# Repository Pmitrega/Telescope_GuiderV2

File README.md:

## Development Environment setup

Setup docker:
<pre>
sudo apt install -y docker.io
sudo usermod -aG docker $USER
exec su -l $USER
docker pull --platform linux/arm64 debian:11
</pre>

Enable multiarchitecture emulation and verify it:
<pre>
docker run --rm --privileged multiarch/qemu-user-static --reset -p yes
docker run --rm --privileged multiarch/qemu-user-static --version
</pre>

Now run crosscompile script, first it setup container with :
<pre>
./cross_compile.sh
</pre>

## Target Environment setup
Setup MQTT broker
<pre>
sudo apt update
sudo apt install -y mosquitto mosquitto-clients
</pre>
Enable mosquitto as service
<pre>
sudo systemctl enable mosquitto
sudo systemctl start mosquitto
sudo systemctl status mosquitto
</pre>
To test broker on one console run:
<pre>
mosquitto_sub -t test/topic
</pre>
On other use, after this message on previous one shoud show.
<pre>
mosquitto_pub -t test/topic -m "Hello MQTT"
</pre>

### Mosquito configuration
Now enable websockets and free access:
<pre>
sudo nano /etc/mosquitto/mosquitto.conf
</pre>
Add following lines:
<pre>
listener 1883
allow_anonymous true
listener 9001
</pre>

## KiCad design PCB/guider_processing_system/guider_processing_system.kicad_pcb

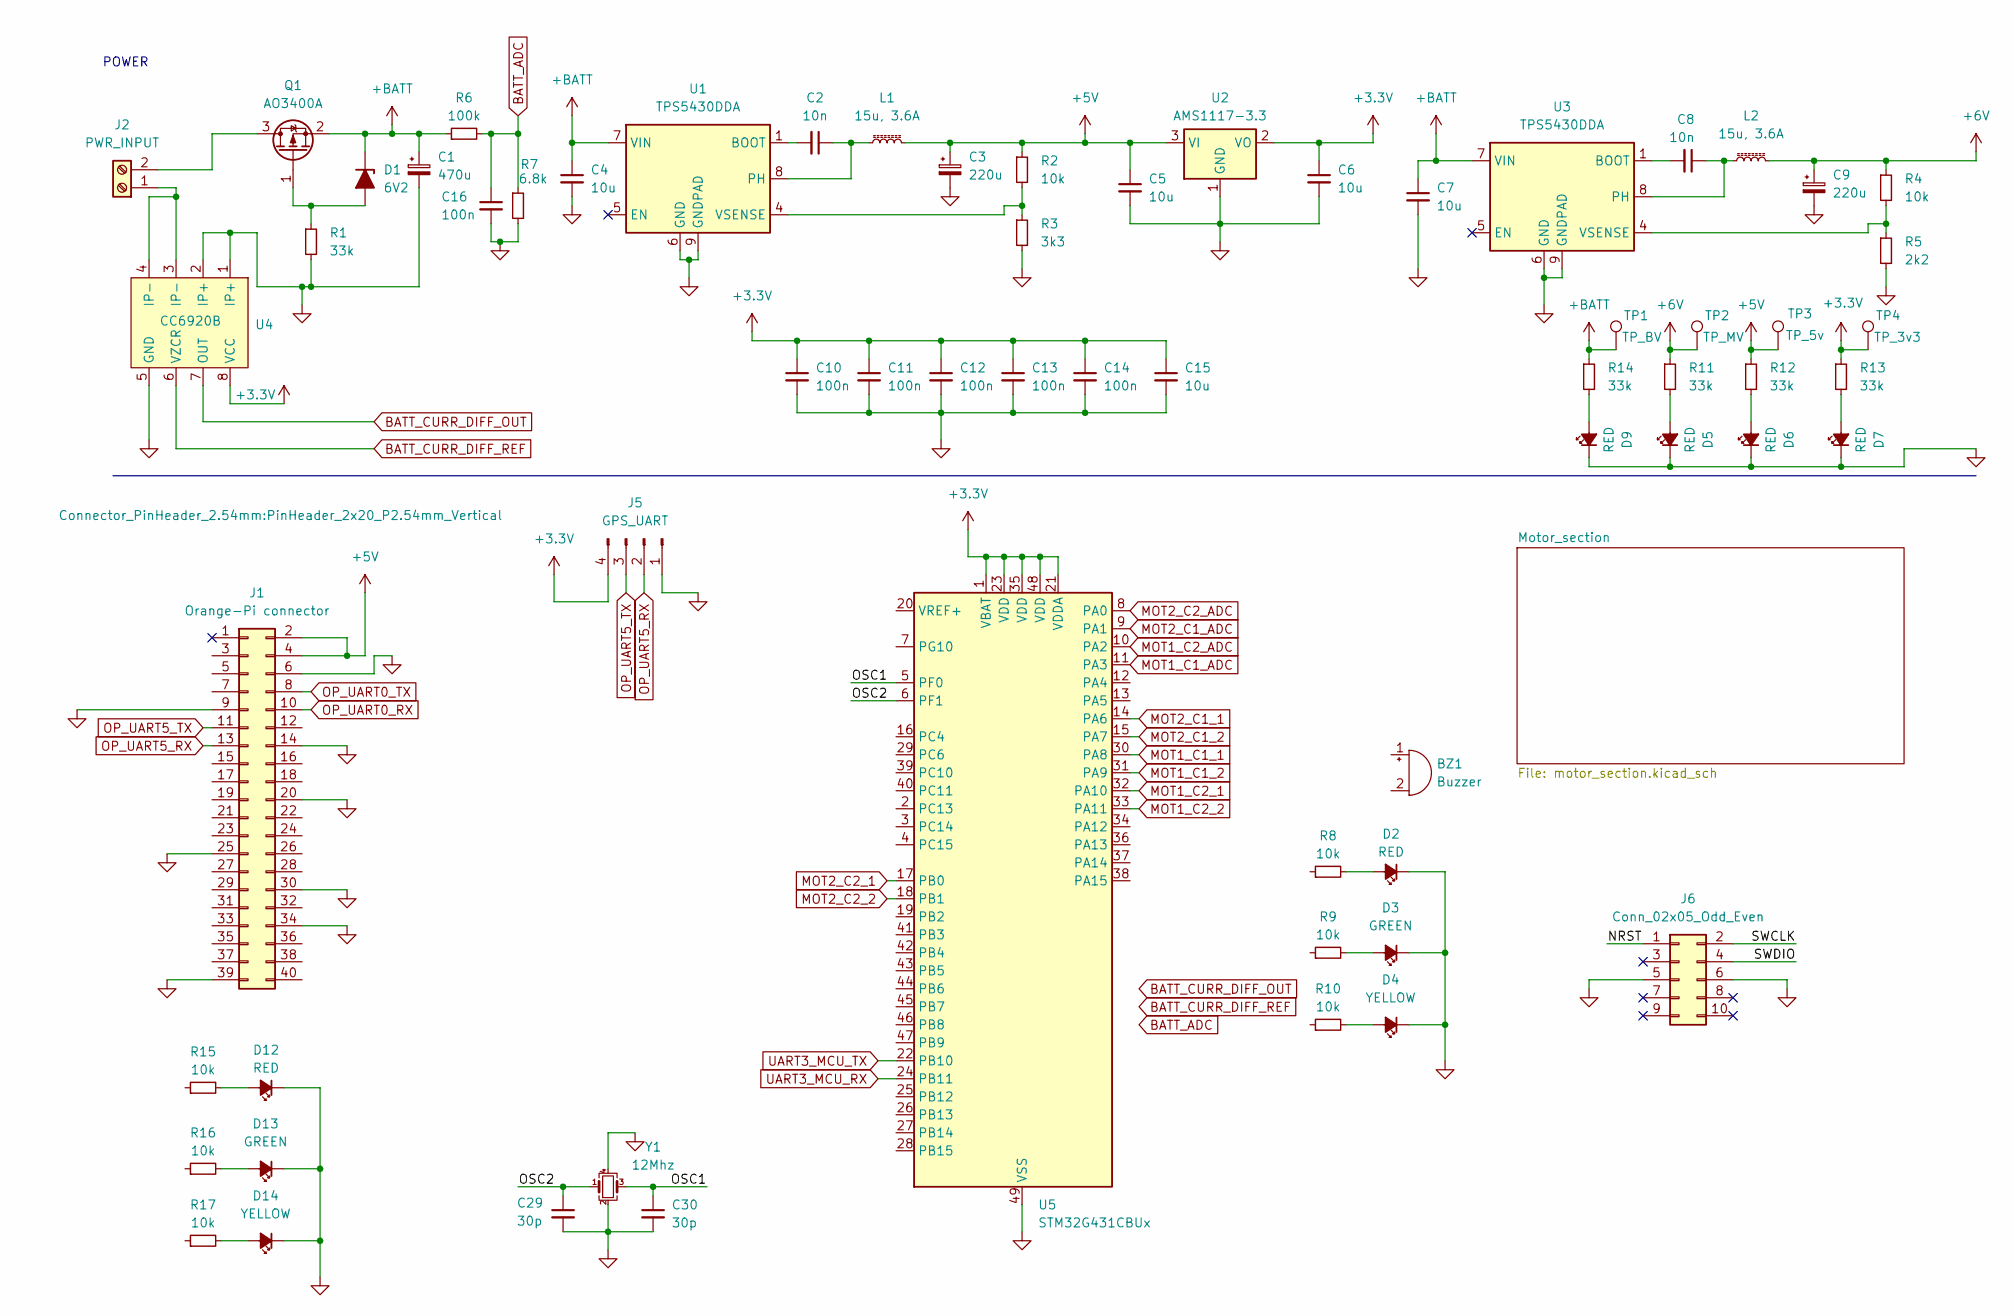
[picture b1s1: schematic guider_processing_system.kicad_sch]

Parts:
BZ1: Buzzer; Buzzer_15x7.5RM7.6
C1: 470u; CP_Radial_D10.0mm_P5.00mm
C2: 10n; C_0603_1608Metric; LCSC C57112
C3, C9: 220u; CP_Radial_D6.3mm_P2.50mm
C4, C7: 10u; C_1206_3216Metric; LCSC C13585
C5, C6, C15: 10u; C_0603_1608Metric; LCSC C1691
C8: 10n; C_0603_1608Metric
C10, C11, C12, C13, C14, C16: 100n; C_0603_1608Metric; LCSC C14663
C29, C30: 30p; C_0603_1608Metric; LCSC C1658
D1: 6V2; D_SOD-323; LCSC C19077457
D2, D5, D6, D7, D9, D12: RED; LED_0805_2012Metric; LCSC C84256
D3, D13: GREEN; LED_0805_2012Metric; LCSC C2297
D4, D14: YELLOW; LED_0805_2012Metric; LCSC C2296
J1: Orange-Pi connector; PinHeader_2x20_P2.54mm_Vertical
J2: PWR_INPUT; TerminalBlock_bornier-2_P5.08mm
J5: GPS_UART; JST_XH_B4B-XH-AM_1x04_P2.50mm_Vertical
J6: Conn_02x05_Odd_Even; IDC-Header_2x05_P2.54mm_Vertical
L1, L2: 15u, 3.6A; L_Sunlord_MWSA1004S; LCSC C436488
Q1: AO3400A; TSOT-23; LCSC C20917
R1, R11, R12, R13, R14: 33k; R_0603_1608Metric; LCSC C4216
R2, R4, R8, R9, R10, R15, R16, R17: 10k; R_0603_1608Metric; LCSC C4216
R3: 3k3; R_0603_1608Metric; LCSC C4216
R5: 2k2; R_0603_1608Metric; LCSC C4216
R6: 100k; R_0603_1608Metric; LCSC C4216
R7: 6.8k; R_0603_1608Metric; LCSC C4216
TP1: TP_BV
TP2: TP_MV
TP3: TP_5v
TP4: TP_3v3
U1, U3: TPS5430DDA; TI_SO-PowerPAD-8_ThermalVias; LCSC C9864
U2: AMS1117-3.3; SOT-223-3_TabPin2; LCSC C6186
U4: CC6920B; SOP-8_3.9x4.9mm_P1.27mm
U5: STM32G431CBUx; QFN-48-1EP_7x7mm_P0.5mm_EP5.6x5.6mm
Y1: 12Mhz; Crystal_SMD_3225-4Pin_3.2x2.5mm; LCSC C9002

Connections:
+3.3V: C6.1, C10.1, C11.1, C12.1, C13.1, C14.1, C15.1, J5.4, R13.1, TP4.1, U2.2 (VO), U4.8 (VCC), U5.1 (VBAT), U5.21 (VDDA), U5.23 (VDD), U5.35 (VDD), U5.48 (VDD)
+5V: C3.1, C5.1, J1.2, J1.4, L1.2, R2.1, R12.1, TP3.1, U2.3 (VI)
+6V: C9.1, L2.2, R4.1, R11.1, TP2.1; also elsewhere on the board
+BATT: C1.1, C4.1, C7.1, D1.1 (K), Q1.2 (S), R6.1, R14.1, TP1.1, U1.7 (VIN), U3.7 (VIN)
/NRST: J6.1
/OSC1: C30.1, U5.5 (PF0), Y1.3
/OSC2: C29.1, U5.6 (PF1), Y1.1
/SWCLK: J6.2
/SWDIO: J6.4
BATT_ADC: C16.1, R6.2, R7.1
BATT_CURR_DIFF_OUT: U4.7 (OUT)
BATT_CURR_DIFF_REF: U4.6 (VZCR)
GND: C1.2, C3.2, C4.2, C5.2, C6.2, C7.2, C9.2, C10.2, C11.2, C12.2, C13.2, C14.2, C15.2, C16.2, C29.2, C30.2, D2.1 (K), D3.1 (K), D4.1 (K), D5.1 (K), D6.1 (K), D7.1 (K), D9.1 (K), D12.1 (K), D13.1 (K), D14.1 (K), J1.6, J1.9, J1.14, J1.20, J1.25, J1.30, J1.34, J1.39, J5.1, J6.5, J6.6, R1.2, R3.2, R5.2, R7.2, U1.6 (GND), U1.9 (GNDPAD), U2.1 (GND), U3.6 (GND), U3.9 (GNDPAD), U4.1 (IP+), U4.2 (IP+), U4.5 (GND), U5.49 (VSS), Y1.2, Y1.4; also elsewhere on the board
MOT1_C1_1: U5.30 (PA8); also elsewhere on the board
MOT1_C1_2: U5.31 (PA9); also elsewhere on the board
MOT1_C2_1: U5.32 (PA10); also elsewhere on the board
MOT1_C2_2: U5.33 (PA11); also elsewhere on the board
MOT2_C1_1: U5.14 (PA6); also elsewhere on the board
MOT2_C1_2: U5.15 (PA7); also elsewhere on the board
MOT2_C2_1: U5.17 (PB0); also elsewhere on the board
MOT2_C2_2: U5.18 (PB1); also elsewhere on the board
unnamed: D1.2 (A), Q1.1 (G), R1.1
unnamed: D2.2 (A), R8.2
unnamed: D3.2 (A), R9.2
unnamed: D4.2 (A), R10.2
unnamed: D5.2 (A), R11.2
unnamed: D6.2 (A), R12.2
unnamed: D7.2 (A), R13.2
unnamed: D9.2 (A), R14.2
unnamed: D12.2 (A), R15.2
unnamed: D13.2 (A), R16.2
unnamed: D14.2 (A), R17.2
unnamed: J2.1, U4.3 (IP-), U4.4 (IP-)
unnamed: J2.2, Q1.3 (D)
unnamed: C2.2, U1.1 (BOOT)
unnamed: C2.1, L1.1, U1.8 (PH)
unnamed: R2.2, R3.1, U1.4 (VSENSE)
unnamed: C8.2, U3.1 (BOOT)
unnamed: C8.1, L2.1, U3.8 (PH)
unnamed: R4.2, R5.1, U3.4 (VSENSE)
OP_UART0_RX: J1.10
OP_UART0_TX: J1.8
OP_UART5_RX: J1.13, J5.2
OP_UART5_TX: J1.11, J5.3
UART3_MCU_RX: U5.24 (PB11)
UART3_MCU_TX: U5.22 (PB10)

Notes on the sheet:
POWER

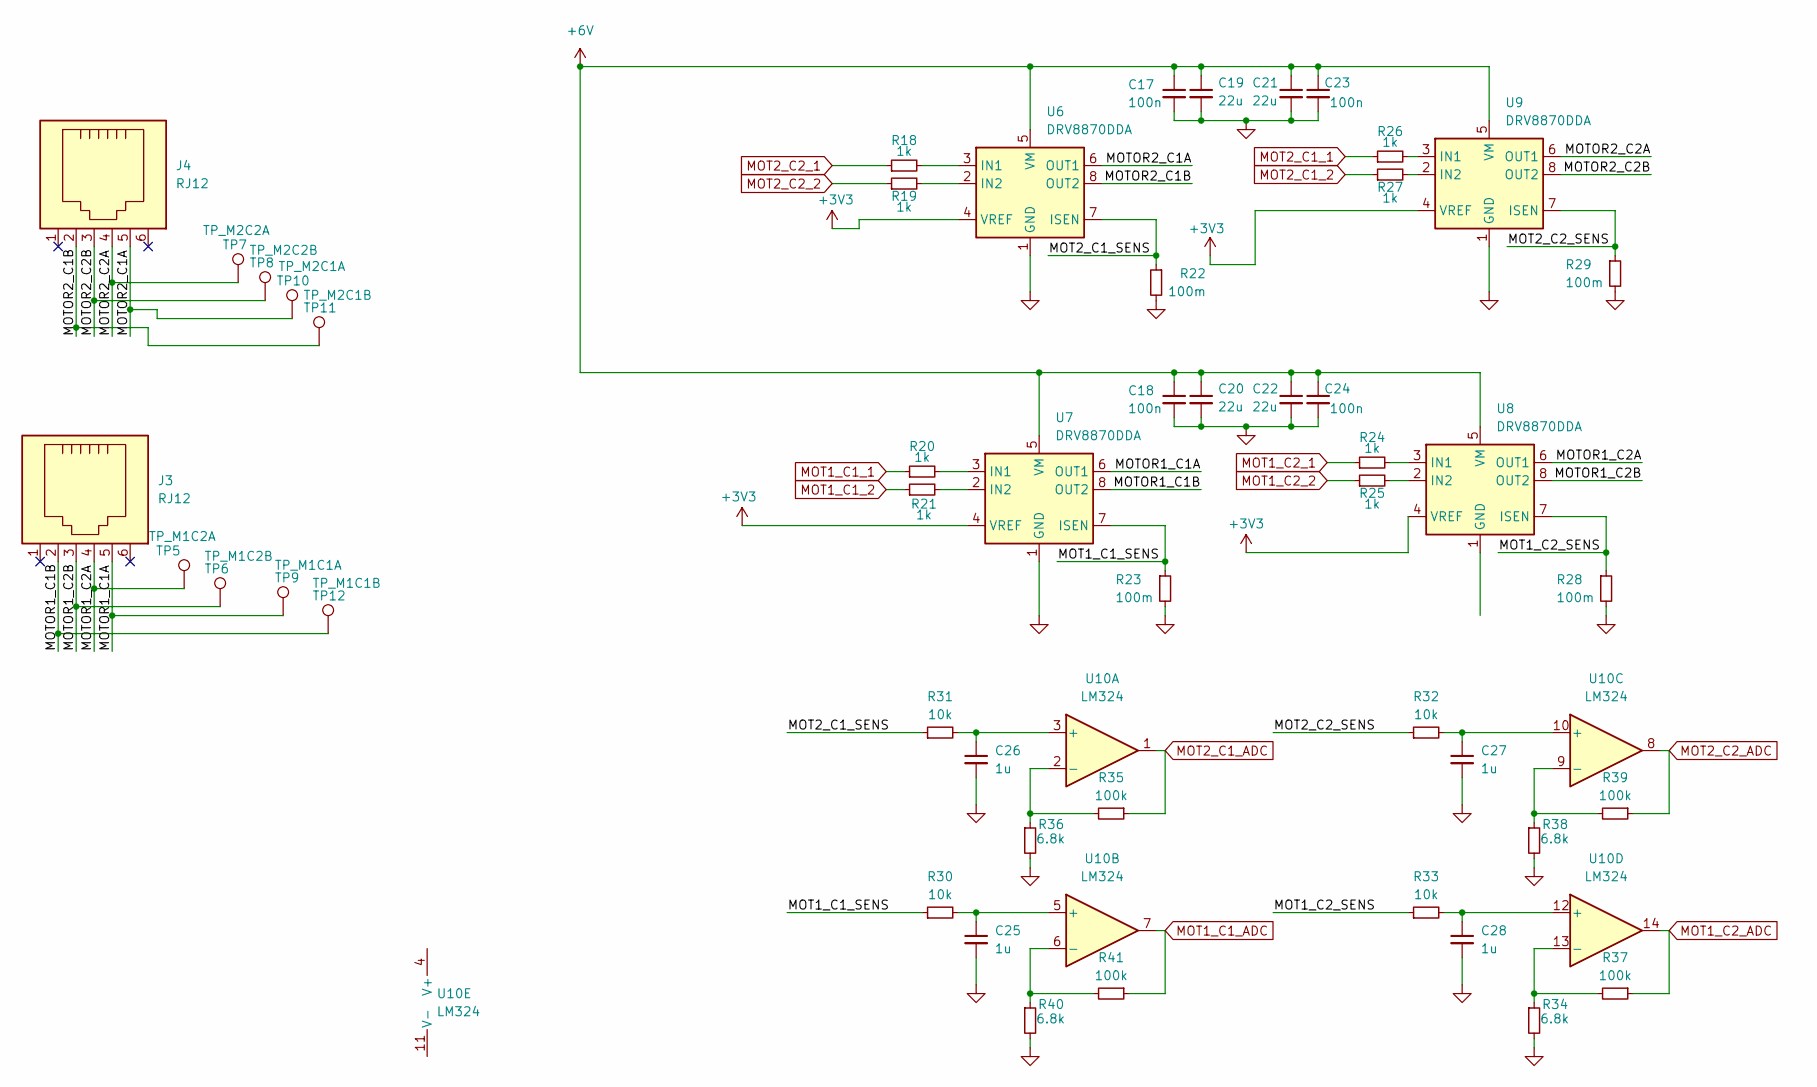
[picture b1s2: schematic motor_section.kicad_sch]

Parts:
C17, C18, C23, C24: 100n; C_0603_1608Metric; LCSC C14663
C19, C20, C21, C22: 22u; L_1210_3225Metric; LCSC C12891
C25, C26, C27, C28: 1u; C_0603_1608Metric; LCSC C15849
J3, J4: RJ12; ST4
R18, R19, R20, R21, R24, R25, R26, R27: 1k; R_0603_1608Metric; LCSC C21190
R22, R23, R28, R29: 100m; R_0603_1608Metric; LCSC C111027
R30, R31, R32, R33: 10k; R_0603_1608Metric; LCSC C4216
R34, R36, R38, R40: 6.8k; R_0603_1608Metric; LCSC C4216
R35, R37, R39, R41: 100k; R_0603_1608Metric; LCSC C4216
TP5: TP_M1C2A; TestPoint_Pad_D1.0mm
TP6: TP_M1C2B; TestPoint_Pad_D1.0mm
TP7: TP_M2C2A; TestPoint_Pad_D1.0mm
TP8: TP_M2C2B; TestPoint_Pad_D1.0mm
TP9: TP_M1C1A; TestPoint_Pad_D1.0mm
TP10: TP_M2C1A; TestPoint_Pad_D1.0mm
TP11: TP_M2C1B; TestPoint_Pad_D1.0mm
TP12: TP_M1C1B; TestPoint_Pad_D1.0mm
U6, U7, U8, U9: DRV8870DDA; Texas_HTSOP-8-1EP_3.9x4.9mm_P1.27mm_EP2.95x4.9mm_Mask2.4x3.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; LCSC C86590
U10: LM324; SOIC-14_3.9x8.7mm_P1.27mm

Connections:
+3V3: U6.4 (VREF), U7.4 (VREF), U8.4 (VREF), U9.4 (VREF)
+6V: C17.1, C18.1, C19.1, C20.1, C21.1, C22.1, C23.1, C24.1, U6.5 (VM), U7.5 (VM), U8.5 (VM), U9.5 (VM); also elsewhere on the board
/Motor_section/MOT1_C1_SENS: R23.1, R30.1, U7.7 (ISEN)
/Motor_section/MOT1_C2_SENS: R28.1, R33.1, U8.7 (ISEN)
/Motor_section/MOT2_C1_SENS: R22.1, R31.1, U6.7 (ISEN)
/Motor_section/MOT2_C2_SENS: R29.1, R32.1, U9.7 (ISEN)
/Motor_section/MOTOR1_C1A: J3.5, TP9.1, U7.6 (OUT1)
/Motor_section/MOTOR1_C1B: J3.2, TP12.1, U7.8 (OUT2)
/Motor_section/MOTOR1_C2A: J3.4, TP5.1, U8.6 (OUT1)
/Motor_section/MOTOR1_C2B: J3.3, TP6.1, U8.8 (OUT2)
/Motor_section/MOTOR2_C1A: J4.5, TP10.1, U6.6 (OUT1)
/Motor_section/MOTOR2_C1B: J4.2, TP11.1, U6.8 (OUT2)
/Motor_section/MOTOR2_C2A: J4.4, TP7.1, U9.6 (OUT1)
/Motor_section/MOTOR2_C2B: J4.3, TP8.1, U9.8 (OUT2)
GND: C17.2, C18.2, C19.2, C20.2, C21.2, C22.2, C23.2, C24.2, C25.2, C26.2, C27.2, C28.2, R22.2, R23.2, R28.2, R29.2, R34.2, R36.2, R38.2, R40.2, U6.1 (GND), U6.9 (GND), U7.1 (GND), U7.9 (GND), U9.1 (GND), U9.9 (GND); also elsewhere on the board
MOT1_C1_1: R20.1; also elsewhere on the board
MOT1_C1_2: R21.1; also elsewhere on the board
MOT1_C1_ADC: R41.1, U10.7
MOT1_C2_1: R24.1; also elsewhere on the board
MOT1_C2_2: R25.1; also elsewhere on the board
MOT1_C2_ADC: R37.1, U10.14
MOT2_C1_1: R26.1; also elsewhere on the board
MOT2_C1_2: R27.1; also elsewhere on the board
MOT2_C1_ADC: R35.1, U10.1
MOT2_C2_1: R18.1; also elsewhere on the board
MOT2_C2_2: R19.1; also elsewhere on the board
MOT2_C2_ADC: R39.1, U10.8
unnamed: R18.2, U6.3 (IN1)
unnamed: R19.2, U6.2 (IN2)
unnamed: R20.2, U7.3 (IN1)
unnamed: R21.2, U7.2 (IN2)
unnamed: U8.1 (GND), U8.9 (GND)
unnamed: R24.2, U8.3 (IN1)
unnamed: R25.2, U8.2 (IN2)
unnamed: R26.2, U9.3 (IN1)
unnamed: R27.2, U9.2 (IN2)
unnamed: C26.1, R31.2, U10.3 (+)
unnamed: R35.2, R36.1, U10.2 (-)
unnamed: C25.1, R30.2, U10.5 (+)
unnamed: R40.1, R41.2, U10.6 (-)
unnamed: C27.1, R32.2, U10.10 (+)
unnamed: R38.1, R39.2, U10.9 (-)
unnamed: C28.1, R33.2, U10.12 (+)
unnamed: R34.1, R37.2, U10.13 (-)

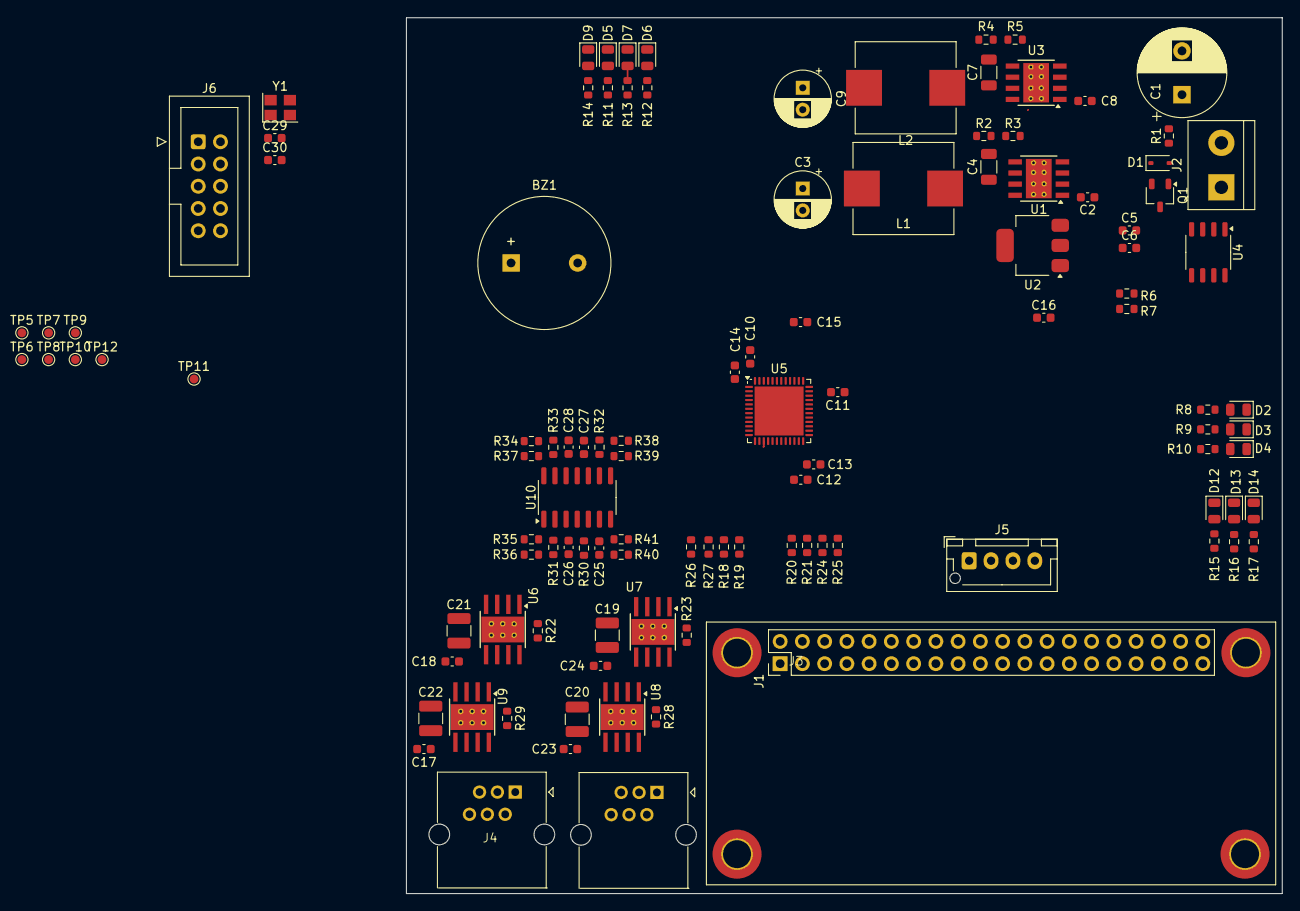
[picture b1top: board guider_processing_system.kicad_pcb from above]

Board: 2 copper layers, 100.0 x 100.0 mm, 111 parts (0 on the bottom side), 71 nets.

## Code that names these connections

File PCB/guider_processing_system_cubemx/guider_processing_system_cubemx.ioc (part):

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Mcu.Name=STM32G431C(6-8-B)Ux
Mcu.Package=UFQFPN48
Mcu.UserName=STM32G431CBUx
PA0.Mode=IN1-Single-Ended
PA0.Signal=ADC1_IN1
PA1.Mode=IN2-Single-Ended
PA1.Signal=ADC1_IN2
PA10.GPIOParameters=GPIO_Label
PA10.GPIO_Label=MOT1_C2_1
PA10.Signal=S_TIM1_CH3
PA11.GPIOParameters=GPIO_Label
PA11.GPIO_Label=MOT1_C2_2
PA11.Signal=S_TIM1_CH4
PA13.Mode=Serial_Wire
PA13.Signal=SYS_JTMS-SWDIO
PA14.Mode=Serial_Wire
PA14.Signal=SYS_JTCK-SWCLK
PA2.Mode=IN3-Single-Ended
PA2.Signal=ADC1_IN3
PA4.GPIOParameters=GPIO_Label
PA4.GPIO_Label=BUZZER
PA4.Signal=COMP_DAC11_group
PA6.GPIOParameters=GPIO_Label
PA6.GPIO_Label=MOT2_C1_1
PA6.Signal=S_TIM3_CH1
PA7.GPIOParameters=GPIO_Label
PA7.GPIO_Label=MOT2_C1_2
PA7.Signal=S_TIM3_CH2
PA8.GPIOParameters=GPIO_Label
PA8.GPIO_Label=MOT1_C1_1
PA8.Signal=S_TIM1_CH1
PA9.GPIOParameters=GPIO_Label
PA9.GPIO_Label=MOT1_C1_2
PA9.Signal=S_TIM1_CH2
PB0.GPIOParameters=GPIO_Label
PB0.GPIO_Label=MOT2_C2_1
PB0.Signal=S_TIM3_CH3
PB1.GPIOParameters=GPIO_Label
PB1.GPIO_Label=MOT2_C2_2
PB1.Signal=S_TIM3_CH4
PB10.Mode=Asynchronous
PB10.Signal=USART3_TX
PB11.Mode=Asynchronous
PB11.Signal=USART3_RX
PF0-OSC_IN.Mode=HSE-External-Oscillator
PF0-OSC_IN.Signal=RCC_OSC_IN
PF1-OSC_OUT.Mode=HSE-External-Oscillator
PF1-OSC_OUT.Signal=RCC_OSC_OUT
RCC.HSE_VALUE=8000000
RCC.SYSCLKFreq_VALUE=16000000
board=custom

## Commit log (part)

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2025-07-18 Initial commit -- functional webside and SVB camera handling
2025-07-18 added PCB project
2025-07-18 fixing scripts to be universal and adding automatic mqtt ip handling
2025-07-23 Added ASI camera support and autostartup
2025-07-23 Adden image exposure status, corrected minor issues
2025-08-23 Adding dummy camera/ added imageprocessing module/ modified image buffer of web page
2025-08-24 Extended image info, sw only shows aviable image types and ranges
2025-08-25 GUI is now dark
2025-08-25 added auto dump
2025-08-25 Auto dump fix
2025-08-25 Added proper numeration and fixed exces cpu usage of python imageTransmiter
2025-08-25 inutual star detection
2025-09-03 Added transmision and handling of star coordinates, fix capture issue, so there gain and exposure was change only after socond image. Also added basic frambuffer handling , noc can conncet to 1080x19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
2025-10-12 fixed non working donwload button
